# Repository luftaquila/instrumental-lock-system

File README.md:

# lookout

## Wiring
```
       [SW]                       ┌─────────┐ 
 +12V ──o/──┬──────────────────┬──┤(+)      │ 
            │                  ─  │        o── NO
            │          1n4007  ^  │        o── COM
            │                  ─  │        o── NC
            │                  ├──┤(-)      │ 
            │                  │  └─────────┘ 
      ┌───────────┐            │    G6S-2-12  
      │   [VIN]   │            │
      │  HC-SR501 │            │ (C)
      │           │       (B)│/ 
      │      [SIG]o──[10k]───┤   2n3904
      │           │          │\          
      │   [GND]   │            │ (E)
      └───────────┘            │
            └──────────────────┴─────── GND
```

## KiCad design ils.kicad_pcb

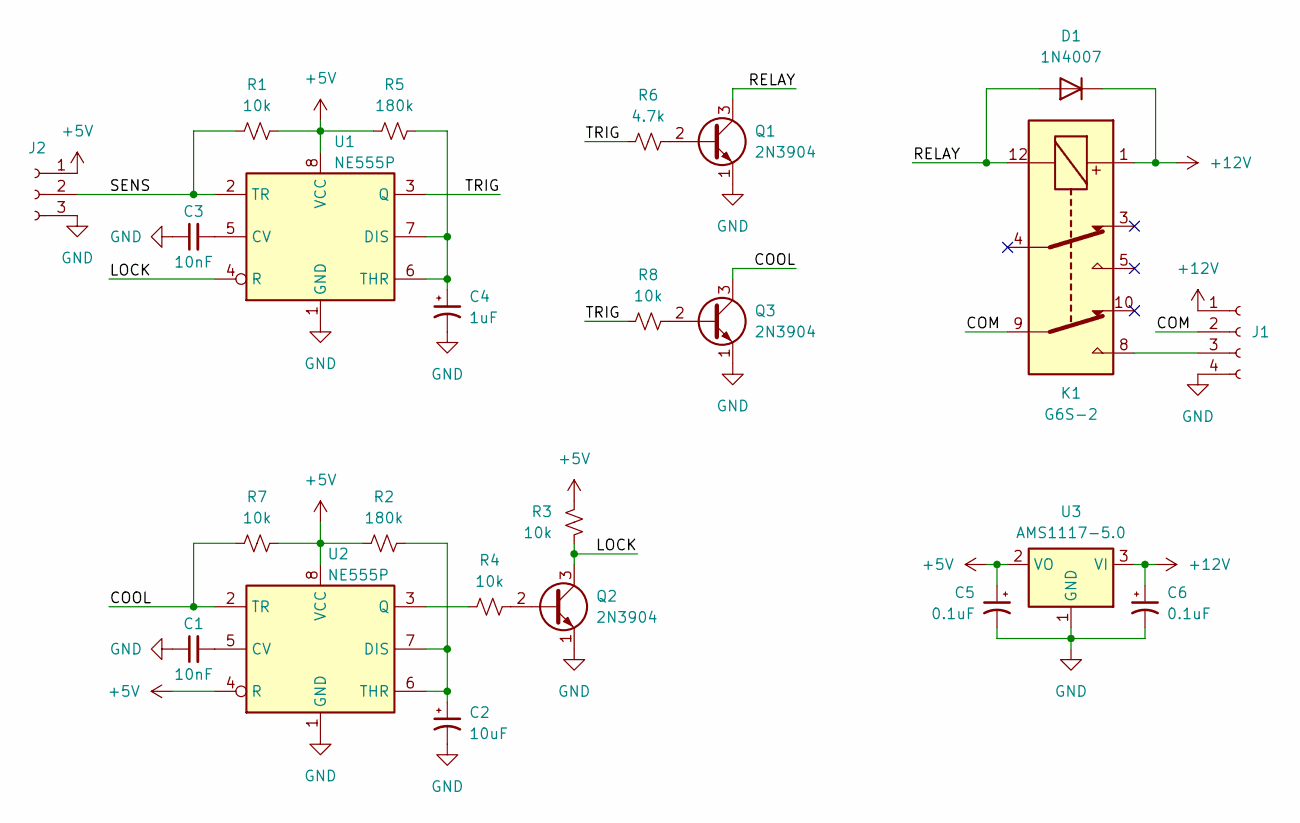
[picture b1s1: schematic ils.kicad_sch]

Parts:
C1, C3: 10nF; C_Disc_D3.0mm_W1.6mm_P2.50mm
C2: 10uF; CP_Radial_D4.0mm_P1.50mm
C4: 1uF; CP_Radial_D5.0mm_P2.50mm
C5, C6: 0.1uF; CP_Radial_D4.0mm_P1.50mm
D1: 1N4007; D_DO-41_SOD81_P10.16mm_Horizontal
J1: Conn_01x04_Socket; PinHeader_1x04_P2.54mm_Vertical
J2: Conn_01x03_Socket; PinHeader_1x03_P2.54mm_Vertical
K1: G6S-2; Relay_DPDT_Omron_G6S-2
Q1, Q2, Q3: 2N3904; TO-92_Inline_Wide
R1, R3, R4, R7, R8: 10k; R_Axial_DIN0207_L6.3mm_D2.5mm_P7.62mm_Horizontal
R2, R5: 180k; R_Axial_DIN0207_L6.3mm_D2.5mm_P7.62mm_Horizontal
R6: 4.7k; R_Axial_DIN0207_L6.3mm_D2.5mm_P7.62mm_Horizontal
U1, U2: NE555P; DIP-8_W7.62mm
U3: AMS1117-5.0; SOT-223-3_TabPin2

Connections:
+5V: C5.1, J2.1, R1.2, R2.1, R3.2, R5.1, R7.2, U1.8 (VCC), U2.4 (R), U2.8 (VCC), U3.2 (VO)
+12V: C6.1, D1.1 (K), J1.1, K1.1, U3.3 (VI)
/COM: J1.2, K1.9
/COOL: Q3.3 (C), R7.1, U2.2 (TR)
/LOCK: Q2.3 (C), R3.1, U1.4 (R)
/RELAY: D1.2 (A), K1.12, Q1.3 (C)
/SENS: J2.2, R1.1, U1.2 (TR)
/TRIG: R6.1, R8.1, U1.3 (Q)
GND: C1.1, C2.2, C3.1, C4.2, C5.2, C6.2, J1.4, J2.3, Q1.1 (E), Q2.1 (E), Q3.1 (E), U1.1 (GND), U2.1 (GND), U3.1 (GND)
unnamed: J1.3, K1.8
unnamed: Q1.2 (B), R6.2
unnamed: Q2.2 (B), R4.2
unnamed: Q3.2 (B), R8.2
unnamed: C3.2, U1.5 (CV)
unnamed: C4.1, R5.2, U1.6 (THR), U1.7 (DIS)
unnamed: C1.2, U2.5 (CV)
unnamed: C2.1, R2.2, U2.6 (THR), U2.7 (DIS)
unnamed: R4.1, U2.3 (Q)

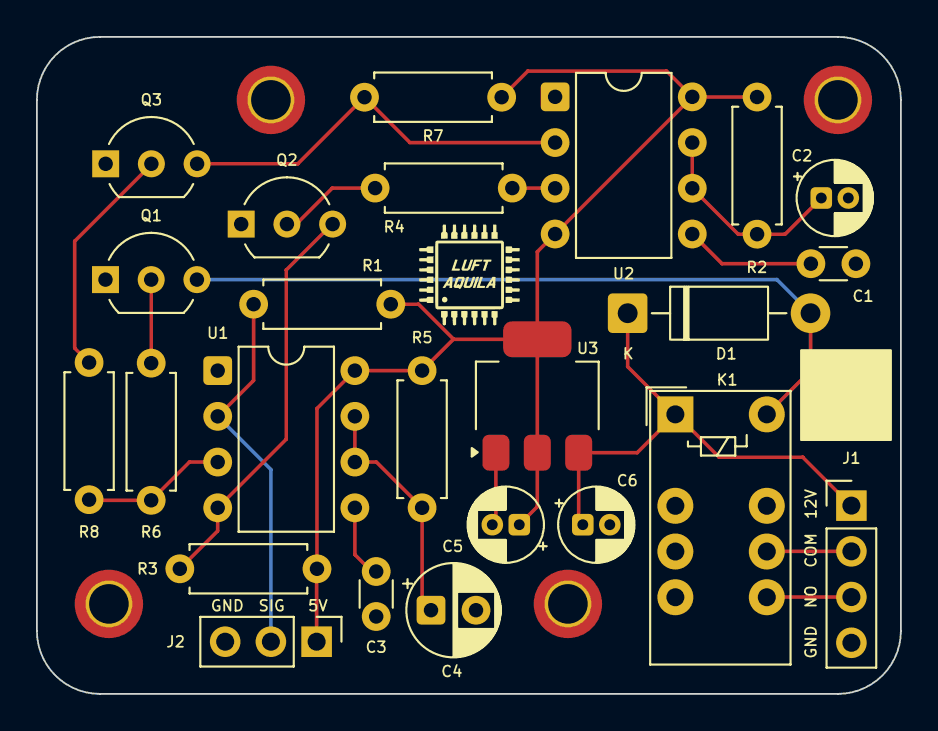
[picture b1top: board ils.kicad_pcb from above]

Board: 2 copper layers, 48.0 x 36.5 mm, 24 parts (0 on the bottom side), 18 nets.

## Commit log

2025-12-23 add: initial design
2025-12-23 add: housing scad
2025-12-23 add: make commands
2025-12-26 update: use HC-SR505
2025-12-26 update: bigger housing for esp01
2026-01-04 update: change sensor to HC-SR501
2026-01-05 add: covers
2026-01-06 add: readme
